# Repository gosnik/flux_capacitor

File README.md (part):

# flux_capacitor

Routing defaults to curved spline/PH realization, enabling compatible erosion and XPBD repair.
Straight routing remains an explicit option (`--straight-tracks`, or
`run_tiers.sh --track-geometry straight`).
Tier promotion still requires complete connectivity and original-project KiCad DRC.

Regional geometry repair enables bounded CPU AVBD refinement after eligible XPBD proposals,
including converged proposals and single-route obstacle scenes. It jointly updates trace controls and eligible generated vias using local blocks,
contact multipliers, adaptive penalties, and deterministic owner coloring under the shared CPU
worker budget. Via motion requires every attachment to be owned by the window; protected or
external attachments pin the via. PH reconstruction and exact copper checks still decide whether
a proposal survives. Use `--no-avbd-relaxation` for comparison or `--avbd-iterations N` (1–128)
to bound its iterations. `regional_avbd_*` metrics distinguish solver proposals from retained
regional improvements; neither implies a final DRC pass.

Regional search evaluates at most two selected windows before broad portfolio enumeration,
with prefix limits of eight alternatives, 1,024 bundle/lane states and 128 access states. Completed
navigation requests and prepared geometry are reused across continuations with exact input keys;
completed-route storage is capped at 512 entries and 64 MiB. The state engine schedules bounded
repair experiments under a shared deadline. Each eligible strategy receives initial exploration;
subsequent priority combines measured physical gain per active time with aging. Stagnation
suppresses only the same strategy and input state. Physical progress affects priority rather
than granting permission to continue. Legacy credit settings no longer gate execution.
Up to two paused experiments retain separate preparation caches. A full pool resumes live work
before admitting another strategy, exchanging slots without evicting the selected continuation.
Changed physical inputs invalidate a
paused regional solve before it can resume. History-only updates preserve its immutable search
snapshot; publication retains newer routing knowledge. Global retries still depend on history. Scheduling history is capped at roughly 4,096 dispatch records;
exact context keys have a 4,096-entry/64 MiB ceiling. Reaching these safety bounds retains the best
checkpoint and reports exhaustion. Linux also checks a cooperative 2 GiB process RSS threshold
when retaining paused experiments; this is not a hard allocator limit.
The engine retains its best physical scene; full-scene connectivity and DRC remain authoritative.

Terrain evolution and hydraulic GPU routing share immutable device-local walkability masks
through the common Vulkan runtime. Cache identity includes dimensions and exact normalized
contents; leases keep buffers alive through fenced submissions. The cache bounds both entries
and allocated device bytes (16 entries / 64 MiB) and evicts only idle entries. Exact host
identity mirrors consume up to another 64 MiB, plus bounded staging during upload. Mutable polygon rasterization uses a
private mask. Height feedback still uploads on every request.
`static_seed_height_evolution_gpu_mask_uploads`, `*_upload_reuses`, and
`*_cross_pipeline_reuses` distinguish transfers, cache hits, and reuse across the two pipelines;
the corresponding `static_seed_hydraulic_gpu_mask_*` counters cover hydraulic discovery.
XPBD retains its existing immutable-input cache. Mutable fields and incompatible geometry
layouts are not aliased across pipelines.

v0.140/schema 21 separates global physical feedback from continuous realization: intermediate
epochs perform bounded discrete corridor, packing, terminal, lane, layer, and via analysis, while
PH/XPBD/PNS, residual repair, quantization, and exact detailed routing run only on the retained
final checkpoint. PH optimization shares an immutable prepared NavMesh corridor, can certify
conservative sub-cell free-space slivers against the exact offset domain, scores seeds against
that same domain, and rejects GPU/CPU candidates that leave the selected homotopy. Exact
connectivity, represented copper DRC, and external KiCad DRC remain authoritative.

Residual regional failures now enter a bounded conflict-directed exact-master loop before the
broader cone/global retry. The existing finite template/access/via/lane CSP is the discrete master;
failed PH/copper realizations contribute stable physical no-good clauses, and only complete route
runs implicated by the failure receive new corridor, homotopy, layer, and via columns. PH geometry
stays outside the master and remains its separation oracle. A replacement is retained only as an
atomic feasibility-first improvement, with exact detailed connectivity and DRC still authoritative.
See [`ADR 0168`](docs/adr/0168-conflict-directed-exact-regional-master.md).

v0.138/schema 21 applies the source-bound KiCad hole-clearance floor as an exact
different-net drill-boundary-to-copper rule for straight tracks, arcs, vias, supported pads, and
saved zone fills. Whole-board and dynamic DRC share that predicate with global and regional route
screening. Mechanically drilled round holes alone participate in hole-to-hole checks; milled oval
holes remain exact copper-clearance obstacles, and laser-drilled microvias stop strict import until
their distinct fabrication semantics are represented. See
[`ADR 0167`](docs/adr/0167-source-bound-fabrication-rules-and-stackup.md).

v0.137/schema 21 preserves the saved physical board thickness and ordered KiCad stackup as
canonical source state. Copper, dielectric, mask, paste, and silkscreen entries retain their
physical order; dielectric `addsublayer` records retain independent material and thickness data;
and dielectric constant/loss tangent use deterministic decimal nanounits rather than binary
floating point. Source-preserving export and telemetry/replay carry the same state. Unrepresented
frequency-dependent dielectric fields stop strict import with an attributed diagnostic instead of
being silently discarded. See
[`ADR 0167`](docs/adr/0167-source-bound-fabrication-rules-and-stackup.md).

v0.136/schema 20 also extends the strict KiCad net-class snapshot to bind the matching saved
project revision and its board-wide fabrication floors. Track, clearance, via diameter, drill, and
annular-ring minima participate in rule resolution; exact circular/oval physical holes participate
in mechanical hole-to-hole DRC and early global/regional via-site rejection. KiCad remains the
project-rule authority, and unrepresented custom or region-dependent rules are not approximated as
if they were exact.

v0.129/schema 19 preserves a KiCad zone that has no saved fill as an immutable
`requires_refill` marker instead of discarding it or inventing copper. Canonical validation keeps
saved-fill and requires-refill states mutually exclusive. Ordinary detailed routing fails closed;
only the explicit `--refillable-zones` workflow may publish provisional copper, and KiCad refill,
strict re-import, connectivity, and external DRC remain mandatory. All nine pinned
KiCadRoutingTools fixtures now pass strict import in their original KiCad 10 syntax. See
[`ADR 0158`](docs/adr/0158-source-bound-unfilled-zones.md).

The same schema retains circular or oval pad-drill width/height and pad-local drill offset. Exact
non-plated circle/capsule obstacles replace the former maximum-diameter circle, and plated-hole
transition reuse now occurs at the physical hole centre rather than the pad anchor. Telemetry and
the viewer carry and render the same rotated drill geometry. See
[`ADR 0159`](docs/adr/0159-exact-pad-drill-geometry.md).

The native C++/Dear ImGui application for live router inspection and JSONL record/replay is
documented in [docs/router-telemetry-viewer.md](docs/router-telemetry-viewer.md). It visualizes
routes, rip-up activity, Pathfinder metrics, congestion and clearance conflicts, resource
occupancy, routing priority, and via-site decisions from `flux.telemetry.v1`.

The v0.128 router-side observer exposes global routing milestones, staged-priority evidence,
regional residual groups, attributed physical conflicts, bounded via candidates, and selected via
assignments through a bounded, read-only Boost.Beast server at
`ws://127.0.0.1:8765/telemetry` by default for KiCad routing and integrated-optimization commands;
`--no-telemetry` is the explicit headless opt-out. A preallocated non-blocking MPSC ring
isolates workers from the observer, while stable-ID coalescing and recovery snapshots let the
viewer recover current state. A separately cached immutable source snapshot supplies the viewer
with board outline/cutouts, layers/nets, footprint courtyards and pads, existing tracks/native arcs,
vias, zones, and keepouts without retransmitting the board in every dynamic snapshot. A stable
path-plus-revision identity lets the same observer retain multiple KiCad source scenes.
Selected global polylines are overlaid as provisional routes even when regional/detailed routing is
incomplete. Complete local quintic PH tessellations, selected regional vias, and their exact-static-
checked straight or dogleg run-ups are separate provisional overlays, so a via relocation is not
displayed as an unconnected marker. Detailed-copper, placement, and validation events remain
incremental follow-up coverage.
The activity table is newest-first, and compact regional `SearchSummary` events keep long PH
window realization observable after the global pass has finished. Chronological trace storage and
replay semantics are unchanged. Search-only bursts do not trigger unchanged recovery snapshots.

Connected coarse topology may proceed to exact detailed materialization when every regional window
has produced one complete atomic PH candidate, even if sampled PathFinder/shadow overflow
remains. Exact connectivity and copper DRC still reject the complete transaction. See
[`ADR 0153`](docs/adr/0153-exact-regional-handoff.md) and
[`ADR 0154`](docs/adr/0154-default-websocket-telemetry.md). Dense-board observability and the
current Freerouting control are recorded in
[`ADR 0155`](docs/adr/0155-dense-board-observability-and-external-control.md).

The optional continuous route representation is a tangent-continuous chain of quintic
Pythagorean-hodograph Bezier segments. PH Hermite interpolation, centripetal/chord parameter
selection, fairness-aware branch ranking, optional bounded geometric-G2 joining, polynomial speed
and arc length, analytical curvature and inflection isolation, and exact rational offsets replace
the former cubic B-spline implementation. XPBD and PNS move interpolation nodes and rebuild the PH
segments; telemetry publishes flattened six-control degree-five spans. Detailed routing uses a
resident Vulkan XPBD whole-chain precondition and candidate-major GPU polishing: every bounded
node-move wave is sampled/ranked on the device, while only a stable four-candidate shortlist pays
the recursive CPU shape/corridor certificate. Fine-grained certificates remain serial because
their recursive long tails measured worse when synchronized per node. Complete same-layer route
chains instead run as bounded parallel tasks against one immutable board snapshot; compact copper
deltas are reduced in stable route order and exact-rechecked before commit. CPU exact geometry,
connectivity, DRC, and commit remain authoritative, and unavailable compute restores the complete
CPU wave. KiCad has no electrical Bézier-track primitive, so each final regional PH candidate is
immediately fitted to native connected track arcs/segments and checked as that exact copper scene.
Native fitting checks quantized join angles and uses tangent-matched biarcs when independent
circle fitting would leave kinks. An ownership-resolved manifest carries those exact pieces into
detailed routing; assembled-scene feedback includes outside-window routes and proposed vias.
Arc navigation obstacles cover the actual sweep rather than filling the supporting circle.
Rational PH offsets remain targeted diagnostics for a rejected native scene rather than the normal
acceptance bottleneck. See [`ADR 0156`](docs/adr/0156-quintic-ph-continuous-routing.md) and
[`ADR 0171`](docs/adr/0171-fair-g2-native-copper-realization.md).
Residual retry now solves only transitive fragment-owner cones, reuses unaffected assignments,
and deterministically remaps derived channel/terminal/via identities before atomic checkpoint
replacement. Telemetry and CLI JSON distinguish reused, recomputed, and withheld assignments.
Prepared output validation and NavMesh routing now share cached polygon bounds, boundary indices,
inline immutable cell collections, and a cutout AABB hierarchy. Regional alternatives use
fail-closed local domains, bounded worker caches, clearance-capped distance queries, and indexed
lane-order screening. The completed isolated-ESC qualification takes 18:08.16 at 264,772 KiB peak
RSS and reports 288 reused plus 15 recomputed cone assignments with none withheld. It is still an
incomplete diagnostic checkpoint: 22 nets are unrouted, sampled overflow is 1,114, and 4,756
clearance-shadow conflicts remain, so no detailed copper or KiCad candidate is produced.

`flux_capacitor` is an experimental C++ engine for integrated PCB component placement
and track routing. Placement and routing share one board model so that routing pressure
can improve placement and bounded placement changes can resolve routing failures.

The current executable baseline provides:

- a versioned C++ board IR with integer-nanometre coordinates, stable typed IDs, and
  board-fixed or footprint-owned layer-aware keepouts, plus per-footprint allowed absolute
  rotations and front/back placement permissions;
- board/footprint/pad/track/via/filled-zone/layer/net models plus canonical
  multiple-net-class membership and inferred differential-pair identity with deterministic,
  per-property priority resolution; saved zone regions retain simple outer contours and exact
  hole contours;
- deterministic transforms and polygon/segment predicates over exact outer-board-minus-cutout
  material;
- structural and placement validation with machine-readable issue codes;
- multilayer connectivity analysis spanning pads, tracks, vias, and immutable physical
  filled-zone polygons;
- explicit pad geometry and board fallback plus per-net-class clearance, track, via,
  drill, and board-edge rules;
- shape-aware internal copper DRC for rotated circle, rectangle, oval, and
  round-rectangle pads, filled copper zones, and independent track/via/pad/pour keepout
  rules, with conservative fallbacks for explicitly lossy shapes;
- deterministic multilayer A* global routing with negotiated edge/node congestion,
  exact board-edge, indexed shape-aware foreign-copper, filled-zone, and track/via keepout
  obstacles,
  orthogonal off-grid pin access, vias, incremental multi-pin trees, capacity overflow,
  stagnation limits, deterministic per-resource demand/contributing-net evidence, and
  affected-cone checkpoint reuse with automatic geometric invalidation; planned width,
  via diameter, and foreign-net spacing use each net's resolved routing rules; conservative
  slicer-inspired scanline decomposition groups distinct free lanes into capacity-bearing
  corridor resources whose present/history congestion participates in PathFinder allocation;
  between unsuccessful passes, deterministic pressure-aware reroute ordering promotes unrouted
  and repeatedly congested nets inside their existing priority tier while keeping declared
  differential pairs and routing buses contiguous and ordered; an opt-in hybrid graph also lets
  PathFinder traverse independently rechecked capacity-bearing Voronoi chords directly instead of
  visiting every intermediate grid sample; explicitly bounded terminal neck-down access may
  recover an ordinary-net pin escape only after nominal width fails, every narrow segment passes
  exact represented clearance, and its grid portal remains legal at nominal width; an independent
  direct-medial policy can allocate a short exact chord at configured narrower demand only when
  nominal demand cannot fit and nominal-width disks remain legal at both transition portals; an
  opt-in stateful sampled-corridor policy constructs a second conservative narrow-width corridor
  graph and lets bounded A* width-mode runs cross multi-edge bottlenecks while charging their own
  physical corridor capacity; when shared medial capacity is enabled, every selected ordinary-net
  width contributes the same `width + 2 * clearance` envelope to PathFinder cost, overflow,
  packing, and checkpoint reuse; an opt-in late constructive phase can reject every transition
  that would exceed sampled, corridor, or selected-width shared physical capacity while retaining
  the best earlier negotiated checkpoint if no strict ordering completes; strict failures also
  retain directed occupying-net evidence, and an independently bounded singleton repair can rip
  complete same-pass blockers, retry first, and defer every victim for a fresh route;
- opt-in transactional KiCad zone-refill routing that treats saved pours as planning-time
  refillable geometry, emits only a provisional result from C++, refills a separate candidate
  through KiCad, and publishes it only after strict re-import and whole-board KiCad DRC;
- deterministic detailed materialization that simplifies global paths into tracks and
  spanning vias, transactionally reuses validated unaffected-net copper with stable IDs,
  falls back to full rematerialization when reuse is invalid, and rejects structurally
  invalid, disconnected, or DRC-illegal results, and materializes per-net resolved
  track/via dimensions unless an explicit run-wide override is requested; deterministic
  45-degree corner pull-tight shortens physical copper and falls back to the legal orthogonal
  route whenever exact checks reject a shortcut; bounded continuous centerline projection then
  shortens conventional polylines inside per-vertex trust regions, using deterministic halving
  to approach obstacle clearance, a run-wide exact-candidate budget, quantized local DRC probes,
  whole-board connectivity/DRC acceptance, and discrete fallback; opt-in strict-medial
  materialization can replace topology-complete resources with checked packed lane chords,
  accepted same-layer
  route-selected junction bridges whose shifted resource lines can meet at checked polyline
  miters, exact terminal joins, and multi-layer runs; complete differential pairs and
  ordered buses can select spacing-checked, order-preserving via arrays as one group transaction;
  mixed-width terminal and direct-medial paths can undergo bounded continuous refinement inside
  equal-width planar runs while every width/layer transition remains fixed, with exact local checks
  and transactional discrete fallback; detailed CLI results retain the governing global status,
  failing-net connectivity details, a copper-violation histogram, and one representative violation
  without exporting an illegal candidate;
  bounded group fanout synthesis preserves legal direct joins or packs ordered staircases at pad
  and layer-run boundaries, can translate a via array longitudinally to create escape run-up, and
  atomically falls back when exact clearance, gap, skew, connectivity, or board DRC rejects every
  candidate; edge-aligned terminal width metadata is simplified only inside equal-width runs and
  materialized as distinct straight KiCad segments; equal-width orthogonal corners can also
  receive deterministic 45-degree pull-tight without moving a width boundary; optional native
  curved fitting likewise operates only within equal-width same-layer runs and inherits that local
  width, while topology-locked replacement remains withheld for that path;
  opt-in post-allocation cubic B-spline routing preserves endpoint tangents, adaptively tessellates
  and fits native lines/arcs, builds exact collision envelopes, invokes bounded recursive PNS
  push-shove for unlocked straight blockers, updates the control corridor, and refits using local
  basis-weighted control displacements; all budgets and whole-transaction polyline fallback remain
  explicit; an independent opt-in
  post-route skew tuner adds ordinary rectangular polyline length to the shorter member of a
  freshly routed point-to-point constrained differential pair, packs one or more deterministic
  periods within explicit amplitude/spacing/candidate bounds, certifies every replacement chord
  against extracted polygonal free space, protects source and reused copper, and commits only after
  exact whole-board acceptance; an independent opt-in batch allocator retains several individually
  legal regions per pair and uses bounded exact conflict search to maximize simultaneously repaired
  pairs instead of committing by greedy pair order;
- deterministic orientation-aware analytical placement using weighted net centroids,
  mixed-size density repulsion, source anchoring, and exact courtyard/board/keepout
  legalization while preserving locked footprints; explicit rigid groups and intersecting
  relative-constraint graphs are projected onto common translations and legalized atomically,
  with one lock immobilizing the complete policy component; an opt-in routing-informed pass feeds
  bounded PathFinder congestion, width-reduction, and blocker escape targets into analytical
  attraction before exact legalization; an independent bounded simultaneous legalizer can assign
  several singleton or policy-component atoms to analytical/routing-guided sites together, making
  occupied-site exchanges legal without exposing an overlapping intermediate placement;
- a bounded deterministic integrated optimizer that tries legal unlocked-footprint moves,
  opt-in discrete rotations and side changes constrained by each footprint's hard orientation
  policy, opt-in atomic position swaps between route-ranked unlocked footprint pairs, and bounded
  rigid translations of explicit designer-declared placement groups; an additional opt-in
  neighborhood translates the complete fixed-point closure of intersecting relative constraints
  and rigid groups as one atomic route-guided component; it can
  evaluate a legalized global placement seed, globally reroutes every proposal,
  runs detailed connectivity and DRC, and accepts only lexicographic feasibility improvements;
  it derives bounded move targets from congestion hot spots, blocking-object geometry, and
  other-pin centroids when the evaluation budget is tight; local candidates use incremental
  global/detailed screening but require a full-board reroute and fresh copper materialization
  before acceptance;
  an explicit routed-quality mode continues beyond first feasibility, reduces actual global
  route cost, and stops only at a bounded local optimum or a truthful pass/evaluation limit;
  equally feasible candidates prefer lower normalized width-loss cost, then actual materialized
  route length, before abstract global search cost;
  every fresh fully routed, connected, and DRC-clean candidate also participates in a bounded
  deterministic Pareto archive across width loss, physical length, route cost, side/rotation
  changes, and placement displacement, without changing the active lexicographic search path;
- optional source-bound placement-move priority sidecars classify every footprint and stage
  cumulative move authorization from resistors and capacitors through transistors, other parts,
  miscellaneous ICs, MCUs, and SoCs, with connectors and pin headers unlocked only as a last
  resort; atomic transactions wait for their highest member tier, while locks and every exact
  placement/routing acceptance gate remain stronger than priority;
- bounded KiCad S-expression parsing and strict `.kicad_pcb` import for layers (including
  `power`-typed inner copper), nets, one outer outline with disjoint board/footprint-owned
  `Edge.Cuts` cutouts, footprints, courtyard provenance, pads, segments,
  track arcs, vias, simple or exactly unfractured saved copper-fill regions, and polygonal
  board/footprint rule areas with all five KiCad keepout categories preserved;
- source-preserving KiCad candidate export with content-derived stale-snapshot checks,
  immutable filled-zone preservation, deterministic UUID mapping, strict semantic round-trip
  verification, and refusal to overwrite an existing artifact;
- deterministic source-bound Specctra DSN export and routing-only SES import for black-box
  freerouting comparison, with exact source/DSN byte provenance, complete placement and protected
  copper verification, 100 nm session-grid checking, normalized deterministic route IDs, full
  connectivity/represented-DRC acceptance, and fail-closed unsupported geometry;
- deterministic source-bound orientation-constraint sidecars with strict stable-ID/reference
  validation, current-only template generation, scoped repair/refinement commands, and safe
  handoff of supported physical changes back to KiCad;
- deterministic source-bound placement-group sidecars with strict stable-ID/reference membership,
  empty non-inferential templates, disjoint group validation, and optimizer-only KiCad policy
  preservation;
- deterministic source-bound placement-region sidecars with explicit world polygons, stable
  footprint membership, full transformed-envelope containment, empty non-inferential templates,
  and hard enforcement across global and integrated placement;
- deterministic source-bound relative-placement sidecars that capture nominal anchor vectors from
  the immutable source and enforce inclusive reviewed X/Y deviation windows across all placement
  paths without inferring relationships from connectivity or proximity; version 2 additionally
  captures nominal radial distance and relative rotation and can enforce optional inclusive
  distance and circular microdegree windows;
- exact source representation of circular KiCad courtyards with conservative circumscribed search
  proxies, plus complete source-bound placement-envelope sidecars whose pad-derived suggestions
  remain unusable until every missing footprint is explicitly reviewed and approved; an
  independent opt-in may instead derive tentative pad/Fab/Silk bounds for proposal generation,
  while marking every resulting placement for mandatory post-process human review;
- a read-only `kicad-python` IPC bridge for explicit project net classes and effective per-net
  constituents, including differential-pair width/gap defaults, with deterministic source-bound
  snapshots consumed by every KiCad routing and optimization command;
- deterministic C++ source/candidate change sets that require byte-for-byte reproduction through
  the source-preserving exporter, inventory every live footprint and routing UUID, and describe
  exact footprint-transform previews plus track, arc, and via create/update/remove operations;
- a fail-closed `kicad-python` candidate bridge whose default mode only previews an exact live-board
  match and whose opt-in routing apply performs a second in-commit stale check, validates every
  returned object, and pushes one unsaved undo step; its offline validation mode exercises the
  current C++ change-set contract without requiring a running editor; live footprint apply remains
  withheld while current upstream whole-footprint updates can damage schematic linkage;
- a minimal routing-only KiCad workflow that packages measured free-space/PathFinder policies as
  the bounded `autoroute_v1` preset, requires a new candidate path, previews a source-bound change
  set, runs external KiCad CLI DRC when available, and permits live routing application only after
  that independent DRC passes;
- a bounded integrated `place_route_v1` KiCad workflow that runs analytical/routing-guided global
  placement and detailed routing together, defaults to the reviewable resistor-first/connector-last
  move policy, verifies a source-bound candidate and external KiCad DRC, reports exact human-review
  reasons, and withholds every placement result from live IPC application;
- deterministic source-bound differential-pair sidecars for explicit minimum physical gap and
  maximum routed skew constraints, applied as hard detailed-routing and optimization acceptance
  gates without pretending preferred KiCad net-class geometry is itself a DRC limit;
- a feasibility-first structured objective vector;
- confined conflict-directed anisotropic hydraulic erosion that produces bounded same-layer
  topology alternatives after an exact regional copper failure, with deterministic CPU/Vulkan
  parity and unchanged polygon, clearance, connectivity, and DRC authority;
- a deterministic CLI demonstration and dependency-free CTest suite.

Safe live footprint transforms, transactional zone refill/editing and ambiguous fill contours,
non-courtyard circular graphics, custom rules, gridless/shove detailed routing, scalable density
models, spatially incremental DRC, and richer PCB electrical constraints are the next milestones.
See
[AGENTS.md](AGENTS.md) for the engineering contract and research-backed roadmap.

Architectural decisions are recorded in [`docs/adr`](docs/adr), beginning with the
canonical board core and negotiated-congestion routing baseline.

## Build and test

Requirements: CMake 3.25+, Ninja, a C++20 compiler, Boost 1.75+ with Boost.JSON, OpenSSL 3,
Vulkan headers/loader, `glslc`, and a Vulkan 1.1 compute-capable GPU with a working driver. GPU
acceleration is a
mandatory Flux runtime requirement: configuration fails without the Vulkan toolchain and routing
fails closed if a compute device cannot execute the startup probe. The deterministic CPU hydraulic
implementation is retained only as a test/oracle backend, not as a production fallback.
Boost.Polygon supplies the permissively licensed integer segment-site Voronoi builder; all
resulting graph chords are quantized and rechecked by Flux before use.

```sh
cmake --preset dev
cmake --build --preset dev
ctest --preset dev
```

An AddressSanitizer/UndefinedBehaviorSanitizer preset is also available on supported
GCC/Clang systems:

```sh
cmake --preset asan
cmake --build --preset asan
ctest --preset asan
```

## CLI baseline

The shortest usable path creates a new routed candidate, verifies its exact source-bound change
set, and runs KiCad CLI DRC when `kicad-cli` is installed:

```sh
python3 plugins/kicad/route_board.py \
  --board board.kicad_pcb \
  --output board.flux-routed.kicad_pcb \
  --flux-cli ./build/dev/flux-cli
```

Add `--capture-netclasses` while the matching saved board is open in KiCad to capture authoritative
project rules through the read-only IPC bridge. Alternatively pass an existing source-bound
snapshot with `--netclasses`. Preview is offline and non-mutating. After reviewing it,
`--apply-routing` applies tracks/arcs/vias to the matching open board as one unsaved undo step and
requires an external KiCad DRC pass. The workflow never saves KiCad and refuses existing output
files.

For an explicit provisional zone-refill transaction with the crossing-safe diagonal graph and
native cubic B-spline/PNS line-arc fitting, use:

```sh
python3 plugins/kicad/route_board.py \
  --board board.kicad_pcb \
  --output board.flux-curved.kicad_pcb \
  --flux-cli ./build/dev/flux-cli \
  --refillable-zones \
  --curved-traces
```

This path always refills zones in a separate file, strictly re-imports it, runs KiCad CLI DRC, and
requires human review. It cannot apply routing directly to the open editor.

For a congested refillable board, add `--repair-sampled-conflicts`. After the negotiated pass it
preserves every unaffected route and visits at most two layer-local conflict tiles in stable
pressure order, with at most 12 hard-capacity passes per cone. Every sampled, shared-physical, and
clearance-shadow participant in the selected cone is invalidated; terminal portals are diversified
and the complete participating nets are rerouted with hard capacity. A non-improving repair is
discarded transactionally.

To inspect an unsuccessful run in KiCad, add `--keep-incomplete-preview` and choose a new output
name. The wrapper retains the materialized layout, reports `ok: false` plus a `review_only`
`incomplete_preview`, and returns Flux's nonzero status. Zone refill, external approval, and live
application are deliberately withheld. The lower-level equivalent is `detail-kicad BOARD
--write-incomplete-preview OUTPUT`.

For integrated placement plus routing, use the same bridge in candidate-only mode:

```sh
python3 plugins/kicad/route_board.py \
  --board board.kicad_pcb \
  --output board.flux-place-routed.kicad_pcb \
  --flux-cli ./build/dev/flux-cli \
  --integrated-placement
```

`place_route_v1` defaults to two placement passes, 64 routed candidate evaluations, routing-guided
global placement, and suggested staged move priorities. Pass a reviewed source-bound policy with
`--placement-move-priorities` to replace the prefix-derived classification. Use
`--tentative-envelopes` only when provisional pad/Fab/Silk bounds and mandatory mechanical review
are acceptable. The output remains a new file-level candidate even after external KiCad DRC;
`--apply-routing` is deliberately rejected in this mode because the live bridge does not mutate
footprints. See [`ADR 0112`](docs/adr/0112-bounded-kicad-place-route-workflow.md).

```sh
./build/dev/flux-cli version
./build/dev/flux-cli demo
./build/dev/flux-cli demo-invalid
./build/dev/flux-cli route-demo
./build/dev/flux-cli route-demo --strict-medial
./build/dev/flux-cli route-demo --strict-medial --direct-medial
./build/dev/flux-cli free-space-demo
./build/dev/flux-cli incremental-route-demo
./build/dev/flux-cli detail-demo
./build/dev/flux-cli detail-demo --strict-medial
./build/dev/flux-cli incremental-detail-demo
./build/dev/flux-cli optimize-demo
./build/dev/flux-cli orientation-optimize-demo
./build/dev/flux-cli group-optimize-demo
./build/dev/flux-cli constraint-global-optimize-demo
./build/dev/flux-cli routing-guided-global-optimize-demo
./build/dev/flux-cli refine-demo
./build/dev/flux-cli global-optimize-demo
./build/dev/flux-cli inspect-kicad board.kicad_pcb
./build/dev/flux-cli inspect-free-space-kicad board.kicad_pcb NET_NAME F.Cu --shared-domain
./build/dev/flux-cli constraints-template-kicad board.kicad_pcb
./build/dev/flux-cli envelopes-template-kicad board.kicad_pcb
./build/dev/flux-cli diffpairs-template-kicad board.kicad_pcb
./build/dev/flux-cli buses-template-kicad board.kicad_pcb
./build/dev/flux-cli placement-move-priorities-template-kicad board.kicad_pcb > board.flux_move_priorities
./build/dev/flux-cli autoroute-kicad board.kicad_pcb board.flux-routed.kicad_pcb
./build/dev/flux-cli route-kicad board.kicad_pcb
./build/dev/flux-cli route-kicad board.kicad_pcb --multisource-steiner
./build/dev/flux-cli route-kicad board.kicad_pcb --atomic-net-trees
./build/dev/flux-cli route-kicad board.kicad_pcb --atomic-net-trees --selective-congestion-reroute
./build/dev/flux-cli route-kicad board.kicad_pcb --atomic-net-trees --selective-congestion-reroute --selective-full-reroute-interval 3
./build/dev/flux-cli route-kicad board.kicad_pcb --max-expansions 10000 --expansion-retry-heuristic-weight-per-mille 10000
./build/dev/flux-cli route-kicad board.kicad_pcb --max-expansions 10000 --expansion-retry-heuristic-weight-per-mille 10000 --reuse-weighted-search-frontier
./build/dev/flux-cli route-kicad board.kicad_pcb --present-congestion-multiplier-per-mille 1300 --max-present-congestion-scale-per-mille 10000 --present-congestion-escalation-start-iteration 4
./build/dev/flux-cli route-kicad board.kicad_pcb --strict-medial --direct-medial
./build/dev/flux-cli route-kicad board.kicad_pcb --terminal-neck-down-width-nm 150000 --max-terminal-neck-down-length-nm 3000000
./build/dev/flux-cli route-kicad board.kicad_pcb --direct-medial --medial-neck-down-width-nm 150000 --max-medial-neck-down-length-nm 3000000
./build/dev/flux-cli route-kicad board.kicad_pcb --corridor-neck-down-width-nm 150000 --max-corridor-neck-down-length-nm 3000000 --max-corridor-neck-down-states 5000000
./build/dev/flux-cli route-kicad board.kicad_pcb --corridor-neck-down-width-nm 150000 --max-corridor-neck-down-length-nm 3000000 --max-corridor-neck-down-states 5000000 --width-reduction-cost-per-grid-step 0
./build/dev/flux-cli route-kicad board.kicad_pcb --max-voronoi-resource-segment-length-nm 1000000
./build/dev/flux-cli detail-kicad board.kicad_pcb
# Default: straight track sections with conventional corner pull-tight.
./build/dev/flux-cli detail-kicad board.kicad_pcb board.straight.kicad_pcb
# Optional retained PH/spline realization:
./build/dev/flux-cli detail-kicad board.kicad_pcb --arcs board.curved.kicad_pcb
./build/dev/flux-cli detail-kicad board.kicad_pcb --netclasses board.flux_netclasses
./build/dev/flux-cli detail-kicad board.kicad_pcb --netclasses board.flux_netclasses --diffpairs board.flux_diffpairs --buses board.flux_buses
./build/dev/flux-cli detail-kicad board.kicad_pcb --diffpairs board.flux_diffpairs --tune-differential-pair-skew
./build/dev/flux-cli detail-kicad board.kicad_pcb --diffpairs board.flux_diffpairs --batch-assign-differential-pair-skew
./build/dev/flux-cli optimize-kicad board.kicad_pcb
./build/dev/flux-cli optimize-kicad board.kicad_pcb --placement-move-priorities board.flux_move_priorities
./build/dev/flux-cli optimize-kicad board.kicad_pcb --suggested-placement-move-priorities
./build/dev/flux-cli optimize-kicad board.kicad_pcb --envelopes board.flux_envelopes
./build/dev/flux-cli optimize-kicad board.kicad_pcb board.optimized.kicad_pcb
./build/dev/flux-cli global-optimize-kicad board.kicad_pcb
./build/dev/flux-cli global-optimize-kicad board.kicad_pcb --assignment-global-placement
./build/dev/flux-cli global-optimize-kicad board.kicad_pcb --tentative-envelopes
./build/dev/flux-cli global-optimize-kicad board.kicad_pcb board.optimized.kicad_pcb
./build/dev/flux-cli constrained-optimize-kicad board.kicad_pcb board.constraints
./build/dev/flux-cli constrained-refine-kicad board.kicad_pcb board.constraints board.refined.kicad_pcb
```

Regional candidate learning-to-rank is an opt-in experiment. Collect exact post-realization labels
without changing candidate order, train the external XGBoost model, then enable advisory ranking:

```bash
./build/dev/flux-cli detail-kicad board.kicad_pcb \
  --regional-candidate-training-data build/regional-candidates.jsonl
python3 tools/train_regional_candidate_ranker.py \
  build/regional-candidates.jsonl --output build/regional-ranker.json
./build/dev/flux-cli detail-kicad board.kicad_pcb \
  --regional-candidate-ranker-model build/regional-ranker.json \
  --regional-candidate-training-data build/regional-ranked-candidates.jsonl
```

Training requires the Python `xgboost` and `numpy` packages; routing does not. The exported model
uses a bounded Flux-owned JSON schema and can only reorder the already retained regional
shortlist. Invalid models restore the deterministic heuristic order, and every candidate that is
tried still passes the unchanged PH/XPBD, quantization, connectivity, copper-DRC, and transaction
gates. CLI JSON reports model loading, scored/reordered candidates, observation writes, and any
fallback diagnostic.

`demo` evaluates a small legal routed board and prints a machine-readable objective.
`demo-invalid` deliberately overlaps two courtyards and exits with status 2.
`route-demo` runs the planning-stage global router on the unrouted demo board.
`free-space-demo` runs the net/layer polygonal extraction, conservative integer offset, and
exact-rechecked Voronoi graph pipeline and reports regions, graph topology, withheld curves, and
peak width-dependent lane capacity. Its diagnostics distinguish unsupported obstacles from
identified conservative envelopes used for curved pads, tracks, and vias.
`incremental-route-demo` moves one terminal, reroutes its affected net, and reuses the
compatible path for a second net from the prior global-route checkpoint.
`detail-demo` materializes the global plan as checked physical copper. `--strict-medial` also
requires audited medial transitions and attempts topology-locked packed-lane copper;
`--direct-medial` opts capacity-certified Voronoi chords into PathFinder adjacency and may be
combined with strict mode. JSON distinguishes accepted lane paths, per-path evidence fallback,
and whole-candidate transactional fallback.
`incremental-detail-demo` preserves the stable track object for an unaffected net while
transactionally replacing the changed net and checking the combined board.
`optimize-demo` demonstrates blocking-object geometry and net context producing a useful
placement proposal under a one-move evaluation budget, followed by rerouting and legality
checks.
`orientation-optimize-demo` explicitly enables a 180-degree alternative on a footprint whose
hard allowed set is `{0, 180}`, and shows an offset surface terminal rotating across an
otherwise impassable routing barrier. Rotation and side search are disabled by default, and
run-wide alternatives cannot bypass per-footprint constraints. Side changes remap front/back
pad and owned-keepout layers internally, but source-preserving KiCad export currently rejects
them because a safe flip must rewrite every layer-bearing footprint construct.
`constraint-global-optimize-demo` projects a three-footprint component formed by an intersecting
rigid group and relative constraint onto one analytical translation, legalizes it atomically, and
accepts the seed only after it repairs two blocked routes. JSON reports component counts and one
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
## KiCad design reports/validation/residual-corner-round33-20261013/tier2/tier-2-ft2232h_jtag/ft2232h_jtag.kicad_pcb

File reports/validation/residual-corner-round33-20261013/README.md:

# Round33 — measured pad-core quantization guard

## Round33 — Geometry-dependent pad quantization bound (2026-10-13)

### Failure
Round32 retains lawful curved Tier2 copper but one residual GND corner cannot pass the strict transaction DRC. All nine radii report324998nm arc-centreline distance versus325000nm required at an axis-aligned rectangular pad. Connectivity and fitted tangents are intact.

### Earliest cause and experiment
The pad-arc distance kernel unconditionally subtracts2nm for vertex quantization, including exactly represented integer pad cores. This is a conservative lower bound, not evidence of actual2nm intrusion. Replace the constant with an upward-rounded bound on the maximum actual vertex rounding displacement. Point/segment/convex polygon distance is Lipschitz under that Hausdorff displacement; subtracting the bound remains conservative and becomes zero when no quantization occurs. Rounded-core radius is unchanged. No clearance tolerance is added, no corner is exempted, and every local transaction still passes strict DRC and pad preservation. Verify exact axis-aligned contact/boundary and rotated fractional geometry before benchmark promotion.

### Results and decision
All11 regression targets and independent implementation review pass. Sequential telemetry Tier0/1 remain byte-identical with zero KiCad DRC and opens (30.879s/106.809s detailed). Frozen source hash verification reports no drift.

Tier2 now passes:131/131 scaffold requests, zero physical opens, zero internal copper violations, zero unrounded bends,421 Beziers/164 arcs/889 tracks/75 vias. All164 residual bend repairs succeed. Authoritative exported KiCad error-severity DRC reports zero violations and opens. Planning161.160s; the separate end-to-end detailed command224.166s, including its own planning. PeakRSS725652KiB. Final copper layers were visually inspected (B.Cu is byte-identical to the previously inspected Round32 image).

The original harness exit1 is solely its intentional promotion guard; independent review confirms a final, non-preview, exported candidate passed all qualification gates. Promote Tier2 to qualified with30 iterations and unlock Tier3. The original exit/result remain unchanged as evidence.

Fresh sequential Tier3 remains51/148 with97 physical opens,279 tracks/20 vias,140.707s, peakRSS559696KiB, iteration limit. No final curved materialization. KRT's matched Tier3 run leaves83 opens in162.172s. Keep this general geometry correction and the Tier2 promotion; Tier3 is the next frontier.

Manifest preflight passes after promotion. Independent Tier3 scaffold export confirms97 opens and only the28 inherited footprint/silkscreen warnings; no added clearance/hole violations.

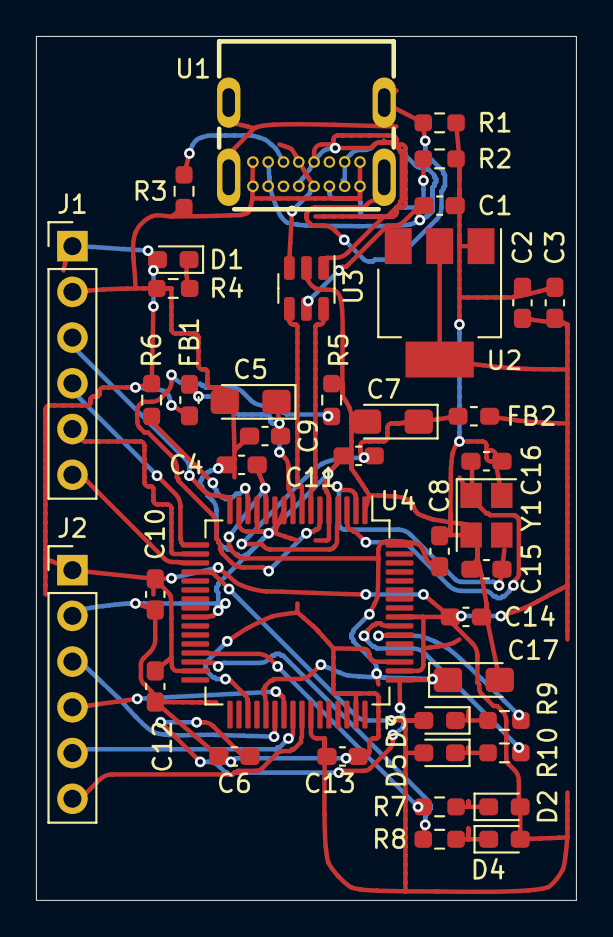
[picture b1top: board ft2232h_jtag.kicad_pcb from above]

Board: 2 copper layers, 30.0 x 48.0 mm, 41 parts (0 on the bottom side), 34 nets.

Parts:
C1, C3: 10uF; C_0603_1608Metric_Pad1.08x0.95mm_HandSolder
C2, C4, C6, C8, C9, C10, C11, C12, C13, C14: 100nF; C_0603_1608Metric_Pad1.08x0.95mm_HandSolder
C5, C7: 4.7uF; CP_EIA-3216-18_Kemet-A_Pad1.58x1.35mm_HandSolder
C15, C16: 30pF; C_0603_1608Metric_Pad1.08x0.95mm_HandSolder
C17: 3.3uF; CP_EIA-3216-18_Kemet-A_Pad1.58x1.35mm_HandSolder
D1, D4, D5: RED; LED_0603_1608Metric_Pad1.05x0.95mm_HandSolder
D2, D3: GREEN; LED_0603_1608Metric_Pad1.05x0.95mm_HandSolder
FB1, FB2: 40@100MHz; L_0603_1608Metric_Pad1.05x0.95mm_HandSolder
J1, J2: Pin Header 2.54 mm; PinHeader_1x06_P2.54mm_Vertical
R1: 0; R_0603_1608Metric_Pad0.98x0.95mm_HandSolder
R2, R3: 5.1k; R_0603_1608Metric_Pad0.98x0.95mm_HandSolder
R4, R6, R7, R8, R9, R10: 1k; R_0603_1608Metric_Pad0.98x0.95mm_HandSolder
R5: 12k; R_0603_1608Metric_Pad0.98x0.95mm_HandSolder
U1: TYPEC-306DDW-ARP16; USB-C-TH_TYPEC-306DDW-ARP16
U2: AMS1117-3.3; SOT-223-3_TabPin2
U3: USBLC6-2SC6; SOT-23-6
U4: FT2232HL; LQFP-64_10x10mm_P0.5mm
Y1: 12MHz; Crystal_SMD_3225-4Pin_3.2x2.5mm

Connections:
+1V8: C4.2, C6.2, C8.2, C17.1, U4.12 (VCORE), U4.37 (VCORE), U4.49 (VREGOUT), U4.64 (VCORE)
+3.3V: C2.1, C3.1, C10.2, C12.2, C13.2, C14.2, D1.2 (A), D2.2 (A), D3.2 (A), D4.2 (A), D5.2 (A), FB1.1, FB2.1, J1.1, J2.1, R6.1, U2.2 (VO), U4.20 (VCCIO), U4.31 (VCCIO), U4.42 (VCCIO), U4.50 (VREGIN), U4.56 (VCCIO)
/OSCI: C15.2, U4.2 (OSCI), Y1.3
/OSCO: C16.2, U4.3 (OSCO), Y1.1
/REF: R5.2, U4.6 (REF)
/RXLED_A: R7.1, U4.29 (ACBUS3)
/RXLED_B: R9.1, U4.54 (BCBUS3)
/TCK_TXD_A: J1.3, U4.16 (ADBUS0)
/TCK_TXD_B: J2.3, U4.38 (BDBUS0)
/TDI_RXD_A: J1.4, U4.17 (ADBUS1)
/TDI_RXD_B: J2.4, U4.39 (BDBUS1)
/TDO_A: J1.5, U4.18 (ADBUS2)
/TDO_B: J2.5, U4.40 (BDBUS2)
/TMS_A: J1.6, U4.19 (ADBUS3)
/TMS_B: J2.6, U4.41 (BDBUS3)
/TXLED_A: R8.2, U4.30 (ACBUS4)
/TXLED_B: R10.2, U4.55 (BCBUS4)
/USB_CONN_D+: U1.A6 (DP1), U1.B6 (DP2), U3.3 (I/O2)
/USB_CONN_D-: U1.A7 (DN1), U1.B7 (DN2), U3.1 (I/O1)
/USB_D+: U3.4 (I/O2), U4.8 (DP)
/USB_D-: U3.6 (I/O1), U4.7 (DM)
/VPHY: C7.1, C11.1, FB2.2, U4.4 (VPHY)
/VPLL: C5.1, C9.1, FB1.2, U4.9 (VPLL)
/~RESET: R6.2, U4.14 (~RESET)
GND: C1.2, C2.2, C3.2, C4.1, C5.2, C6.1, C7.2, C8.1, C9.2, C10.1, C11.2, C12.1, C13.1, C14.1, C15.1, C16.1, C17.2, J1.2, J2.2, R1.2, R2.2, R3.2, R4.1, R5.1, U1.A1 (GND), U1.A12 (GND), U1.B1 (GND), U1.B12 (GND), U2.1 (GND), U3.2 (GND), U4.1 (GND), U4.5 (GND), U4.10 (AGND), U4.11 (GND), U4.13 (TEST), U4.15 (GND), U4.25 (GND), U4.35 (GND), U4.47 (GND), U4.51 (GND), Y1.2, Y1.4
unnamed: D1.1 (K), R4.2
unnamed: D2.1 (K), R7.2
unnamed: D3.1 (K), R9.2
unnamed: D4.1 (K), R8.1
unnamed: D5.1 (K), R10.1
unnamed: R2.1, U1.A5 (CC1)
unnamed: R3.1, U1.B5 (CC2)
unnamed: R1.1, U1.17 (SHIELD), U1.18 (SHIELD), U1.19 (SHILED), U1.20 (SHIELD)
VBUS: C1.1, U1.A4 (VBUS), U1.A9 (VBUS), U1.B4 (VBUS), U1.B9 (VBUS), U2.3 (VI), U3.5 (VBUS)

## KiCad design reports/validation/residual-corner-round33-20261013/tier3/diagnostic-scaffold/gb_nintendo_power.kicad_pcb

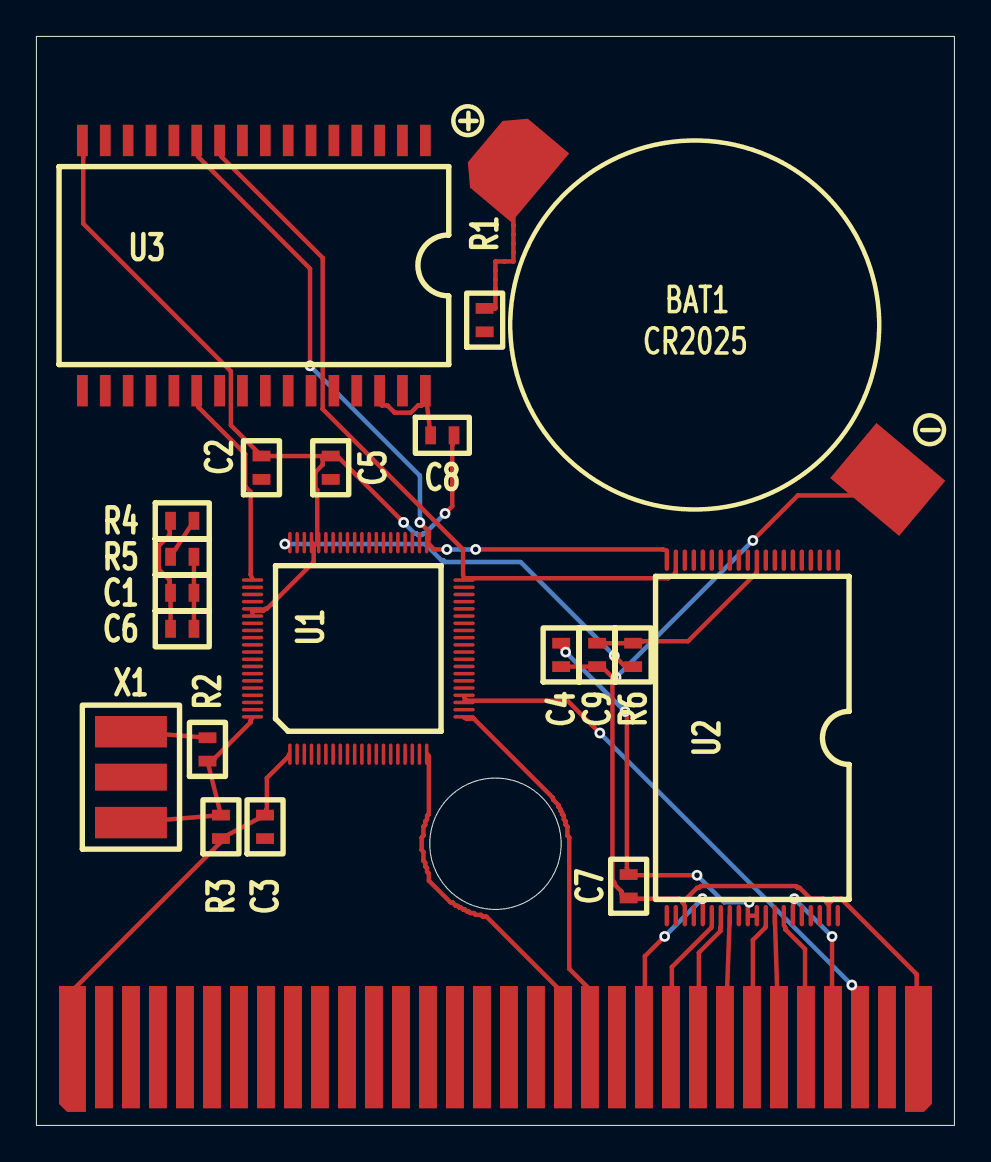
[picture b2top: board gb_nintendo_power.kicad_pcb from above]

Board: 2 copper layers, 51.0 x 60.5 mm, 22 parts (0 on the bottom side), 65 nets.

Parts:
BT1: CR2025; CR2025 Battery
C1: 150 nF; SMD Passive
C2: 120 nF; SMD Passive
C3, C4, C5, C6, C7, C8: 10 nF; SMD Passive
C9: DNP; SMD Passive
Hole: MountingHole_8.4mm_M8
J1: Cart_Edge_Connector; Edge Connector
R1: 1 kOhm; SMD Passive
R2, R4: DNP; SMD Passive
R3: 10kOhm; SMD Passive
R5: 10 kOhm; SMD Passive
R6: 0; SMD Passive
U1: G-MMC1
U2: FLASH
U3: SRAM
X1: Unpopulated; Crystal

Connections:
/A0.Out: U1.25 (A0.Out), U2.21 (A0), U3.12 (A0)
/A0.Sys: J1.6 (A0), U1.6 (A0.Sys)
/A1.Out: U1.41 (A1.Out), U2.20 (A1), U3.11 (A1)
/A1.Sys: J1.7 (A1), U1.7 (A1.Sys)
/A2.Out: U1.40 (A2.Out), U2.19 (A2), U3.10 (A2)
/A2.Sys: J1.8 (A2), U1.8 (A2.Sys)
/A3.Out: U1.39 (A3.Out), U2.18 (A3), U3.9 (A3)
/A3.Sys: J1.9 (A3), U1.9 (A3.Sys)
/A4.Out: U1.36 (A4.Out), U2.17 (A4), U3.8 (A4)
/A4.Sys: J1.10 (A4), U1.10 (A4.Sys)
/A5.Out: U1.35 (A5.Out), U2.16 (A5), U3.7 (A5)
/A5.Sys: J1.11 (A5), U1.11 (A5.Sys)
/A6.Out: U1.34 (A6.Out), U2.15 (A6), U3.6 (A6)
/A6.Sys: J1.12 (A6), U1.13 (A6.Sys)
/A7.Out: U1.32 (A7.Out), U2.14 (A7), U3.5 (A7)
/A7.Sys: J1.13 (A7), U1.14 (A7.Sys)
/A8.Out: U1.31 (A8.Out), U2.8 (A8), U3.27 (A8)
/A8.Sys: J1.14 (A8), U1.15 (A8.Sys)
/A9.Out: U1.30 (A9.Out), U2.7 (A9), U3.26 (A9)
/A9.Sys: J1.15 (A9), U1.16 (A9.Sys)
/A10.Out: U1.37 (A10.Out), U2.36 (A10), U3.23 (A10)
/A10.Sys: J1.16 (A10), U1.17 (A10.Sys)
/A11.Out: U1.29 (A11.Out), U2.6 (A11), U3.25 (A11)
/A11.Sys: J1.17 (A11), U1.18 (A11.Sys)
/A12.Out: U1.27 (A12.Out), U2.5 (A12), U3.4 (A12)
/A12.Sys: J1.18 (A12), U1.19 (A12.Sys)
/A13.Out: U1.26 (A13.Out), U2.4 (A13), U3.28 (A13)
/A13.Sys: J1.19 (A13), U1.20 (A13.Sys)
/A14.Out: U1.42 (A14.Out), U2.3 (A14), U3.3 (A14)
/A14.Sys: J1.20 (A14), U1.21 (A14.Sys)
/A15.Out: U1.43 (A15.Out), U2.2 (A15), U3.31 (A15)
/A15.Sys: J1.21 (A15), U1.22 (A15.Sys)
/A16.Out: U1.44 (A16.Out), U2.1 (A16), U3.2 (A16)
/A17.Out: U1.45 (A17.Out), U2.40 (A17)
/A18.Out: U1.46 (A18.Out), U2.13 (A18)
/A19.Out: U1.47 (A19.Out), U2.37 (A19)
/Batt.VCC: R1.1, U1.62 (Batt.VCC)
/D0: J1.22 (Data_0), U1.75 (D0), U2.25 (D0), U3.13 (D0)
/D1: J1.23 (Data_1), U1.76 (D1), U2.26 (D1), U3.14 (D1)
/D2: J1.24 (Data_2), U1.77 (D2), U2.27 (D2), U3.15 (D2)
/D3: J1.25 (Data_3), U1.74 (D3), U2.28 (D3), U3.17 (D3)
/D4: J1.26 (Data_4), U1.73 (D4), U2.32 (D4), U3.18 (D4)
/D5: J1.27 (Data_5), U1.72 (D5), U2.33 (D5), U3.19 (D5)
/D6: J1.28 (Data_6), U1.71 (D6), U2.34 (D6), U3.20 (D6)
/D7: J1.29 (Data_7), U1.70 (D7), U2.35 (D7), U3.21 (D7)
/GND: BT1.2 (-), C1.1, C2.2, C3.1, C4.1, C5.2, C6.1, C7.1, C8.2, C9.1, J1.32 (GND), R4.1, U1.2 (GND), U1.12 (GND), U1.28 (GND), U1.38 (GND), U1.48 (GND), U1.56 (GND), U1.57 (GND), U1.65 (GND), U1.66 (GND), U1.68 (GND), U1.78 (GND), U2.23 (GND), U2.39 (GND), U3.16 (GND), X1.2
/P10.R6: R6.1, U1.60 (Flash.P10.R6)
/SRAM.VCC: C8.1, U1.64 (SRAM.VOUT), U3.30 (CE2), U3.32 (VCC)
/SRAM.~CE1: U1.61 (SRAM.~CE1), U3.22 (~CE1)
/VCC: C1.2, C3.2, C4.2, C5.1, C6.2, C7.2, J1.1 (+5V), R3.1, R5.2, U1.1 (VCC), U1.33 (VCC), U1.53 (VCC), U1.63 (VCC), U1.69 (VCC), U2.30 (VCC), U2.31 (VCC)
/~CS.Sys: J1.5 (CS), U1.5 (~CS.Sys)
/~Flash.CE: U1.49 (Flash.~CE), U2.22 (~CE)
/~Flash.Reset: C9.2, R6.2, U1.55 (Flash.~RESET), U2.10 (~RESET)
/~Flash.WP: U1.50 (Flash.~WP), U2.12 (~WP)
/~OE.Out: U1.51 (~OE.Out), U2.24 (~OE), U3.24 (~OE)
/~Read.Sys: J1.4 (Read), U1.4 (~Read.Sys)
/~Reset.Sys: J1.30 (Reset), U1.23 (~Reset.Sys), U1.24 (~Reset.Sys)
/~WE.Out: U1.52 (~WE.Out), U2.9 (~WE), U3.29 (~WE)
/~Write.Sys: J1.3 (Write), U1.3 (~Write.Sys)
unnamed: BT1.1 (+), R1.2
unnamed: C2.1, U1.59
unnamed: R4.2, R5.1, U1.67
unnamed: R2.1, R3.2, U1.80 (Clk.In), X1.1
unnamed: R2.2, U1.79 (Clk.Out), X1.3
unnamed: U1.54, U1.58

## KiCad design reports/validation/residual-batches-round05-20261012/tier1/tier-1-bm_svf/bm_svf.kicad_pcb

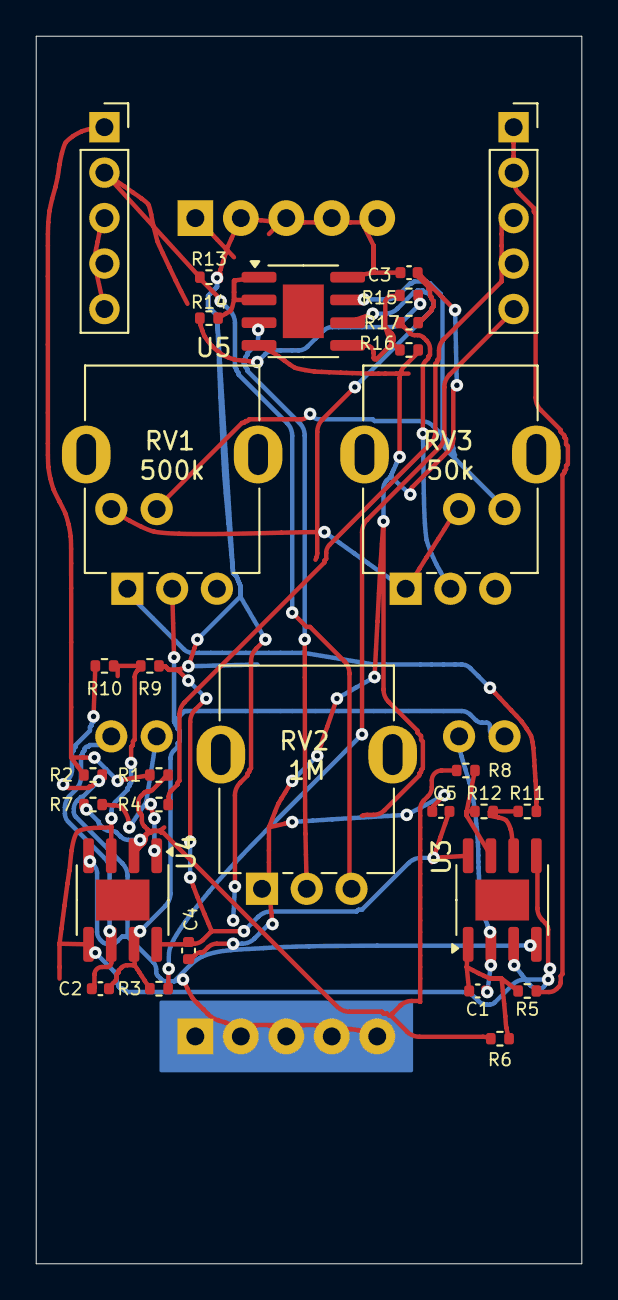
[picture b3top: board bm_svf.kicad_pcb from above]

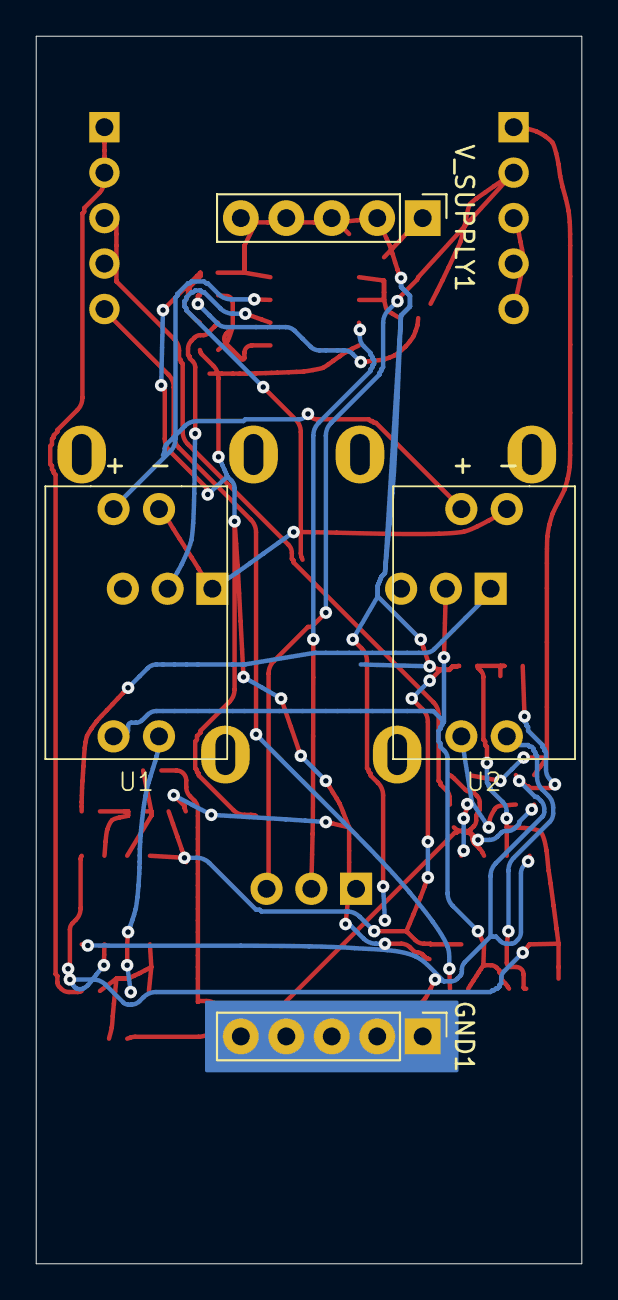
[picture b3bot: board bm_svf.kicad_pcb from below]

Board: 2 copper layers, 30.5 x 68.6 mm, 34 parts (4 on the bottom side), 25 nets.

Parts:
C1, C2: 10nf; C_0402_1005Metric
C3, C4, C5: 0.1uf; C_0402_1005Metric
GND1: Conn_01x05_Pin; Power_Connector
INPUT1: Conn_01x05_Socket; PinSocket_1x05_P2.54mm_Vertical
OUTPUT1: Conn_01x05_Socket; PinSocket_1x05_P2.54mm_Vertical
R1, R11, R12: 51k; R_0402_1005Metric
R2: 22k; R_0402_1005Metric
R3, R4, R5, R9, R10, R14: 1k; R_0402_1005Metric
R6, R7, R8: 10k; R_0402_1005Metric
R13: 100k; R_0402_1005Metric
R15, R16: 1M; R_0402_1005Metric
R17: 5.1k; R_0402_1005Metric
RV1: 500k; Potentiometer_RV09
RV2: 1M; Potentiometer_RV09
RV3: 50k; Potentiometer_RV09
U1, U2: VTL5C
U3, U4, U5: MCP6002-xSN; SOIC-8-1EP_3.9x4.9mm_P1.27mm_EP2.29x3mm
V_SUPPLY1: Conn_01x05_Pin; Power_Connector

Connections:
GND: C3.2, C4.2, C5.2, GND1.1, GND1.2, GND1.3, GND1.4, GND1.5, R2.1, R10.2, R16.1, R17.1, RV2.1, U3.4 (V-), U4.4 (V-), U5.4 (V-)
unnamed: C1.2, R5.1, R6.1, U3.1
unnamed: C2.2, R3.1, RV1.2, U1.4, U4.7
unnamed: INPUT1.3, INPUT1.4, INPUT1.5
unnamed: R4.1, R7.2, U2.4, U4.1
unnamed: R11.2, RV1.1
unnamed: R8.1, R12.1, U3.7
unnamed: R14.1, R15.2
unnamed: R17.2, RV3.2
unnamed: C1.1, U1.3, U3.2 (-)
unnamed: R11.1, R12.2, U3.6 (-)
unnamed: R1.2, R6.2, R7.1, R8.2, U4.2 (-)
unnamed: C2.1, U2.3, U4.6 (-)
unnamed: RV2.2, U5.3 (+)
unnamed: R14.2, U5.1, U5.2 (-)
unnamed: R15.1, R16.2, U5.5 (+)
VACTROL_NEG: RV3.1, U1.1 (-), U2.1 (-), U5.6 (-)
VACTROL_POS: U1.2 (+), U2.2 (+), U5.7
V_BF: OUTPUT1.5, R3.2
V_CV: INPUT1.2, R13.1, RV2.3
V_HF: OUTPUT1.3, OUTPUT1.4, R4.2
V_IN: INPUT1.1, R1.1, R2.2
V_LF: OUTPUT1.1, OUTPUT1.2, R5.2
V_MID: R9.2, R10.1, U3.3 (+), U3.5 (+), U4.3 (+), U4.5 (+)
V_SUPPLY: C3.1, C4.1, C5.1, R9.1, R13.2, U3.8 (V+), U4.8 (V+), U5.8 (V+), V_SUPPLY1.1, V_SUPPLY1.2, V_SUPPLY1.3, V_SUPPLY1.4, V_SUPPLY1.5

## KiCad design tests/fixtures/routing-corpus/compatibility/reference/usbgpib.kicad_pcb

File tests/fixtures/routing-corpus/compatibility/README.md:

# Retained source-compatibility boards

The previous routing Tiers 2–4 remain here with their original manifest entries,
project settings, normalized references, licenses and hash checks. They have
8 / 3 / 17 known structural blockers and are retained for importer/geometry
regression work. Their replacement routing inputs are documented in
`../alternatives/README.md`. No source rules or placements were edited.

Run the existing verifier with `--corpus tests/fixtures/routing-corpus/compatibility
--level all --preflight-only` and a fresh artifact destination. A successful
compatibility preflight checks the recorded allowances; it does not mean these
boards are physically valid or routed.

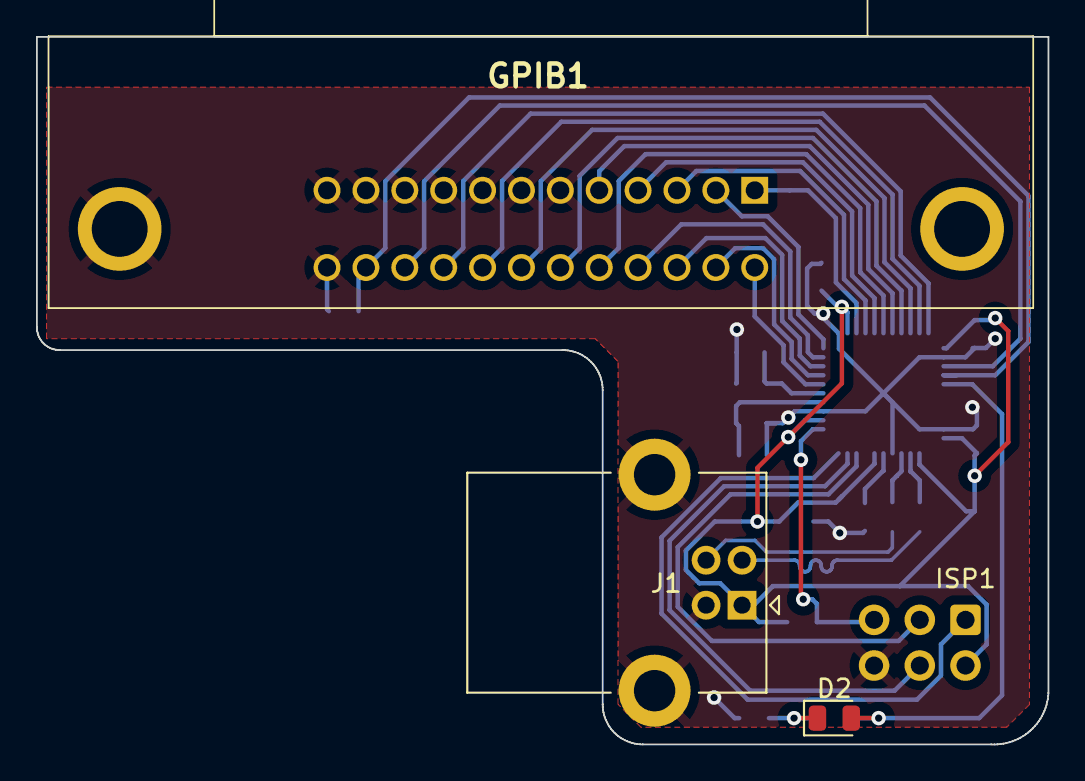
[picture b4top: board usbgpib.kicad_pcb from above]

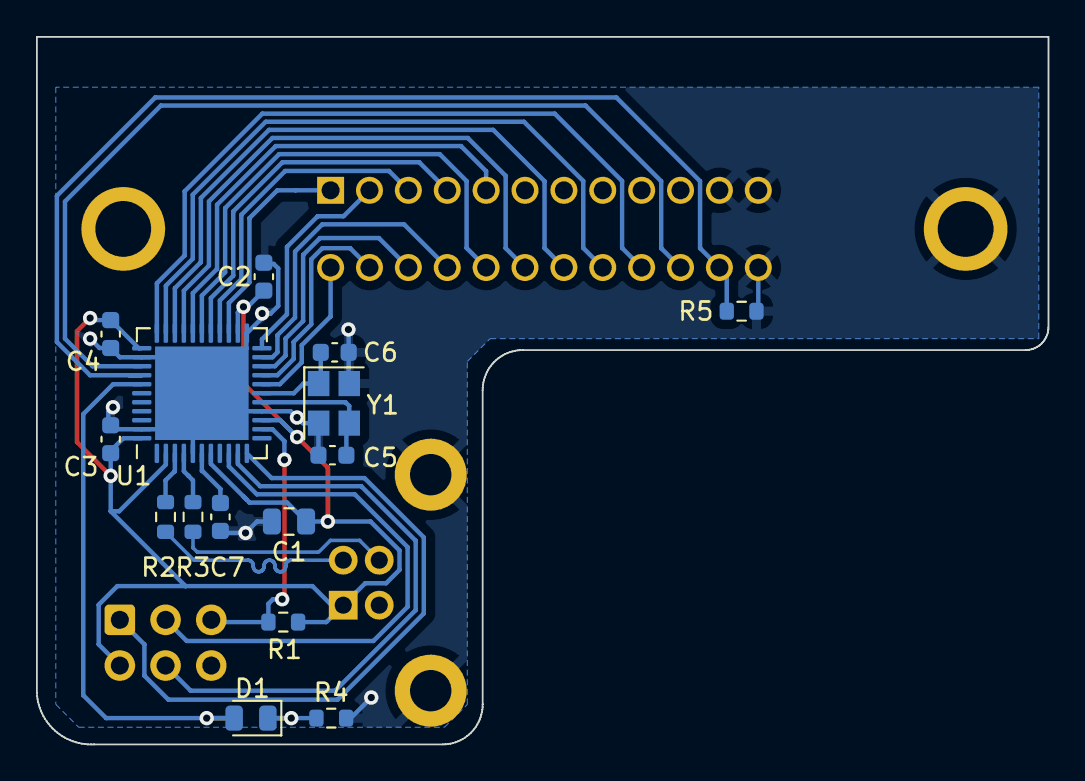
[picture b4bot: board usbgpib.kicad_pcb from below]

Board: 2 copper layers, 56.2 x 39.3 mm, 19 parts (15 on the bottom side), 31 nets.

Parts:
C1: 4.7uF; C_0805_2012Metric
C2, C3, C4: 100nF; C_0603_1608Metric
C5, C6: 22pf; C_0603_1608Metric
C7: 1u; C_0603_1608Metric
D1: LED; LED_0805_2012Metric
D2: DNP; LED_0805_2012Metric
GPIB1: 112-024-113R001; 112024113R001
ISP1: ISP; IDC-Header_2x03_P2.54mm_Vertical
J1: USB_B; USB_B_Lumberg_2411_02_Horizontal
R1: 10k; R_0603_1608Metric
R2, R3: 22R; R_0603_1608Metric
R4: 470R; R_0603_1608Metric
R5: 100k; R_0603_1608Metric
U1: ATmega32U4-MU; QFN-44-1EP_7x7mm_P0.5mm_EP5.2x5.2mm
Y1: Crystal_GND24; Crystal_SMD_3225-4Pin_3.2x2.5mm

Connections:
+5V: C1.1, C2.1, C3.1, C4.1, ISP1.2, J1.1, R1.1, U1.2, U1.7, U1.14, U1.24, U1.34, U1.44
/ATN: GPIB1.22, R5.1, U1.37
/DAV: GPIB1.12, U1.30
/DIO1: GPIB1.2, U1.18
/DIO2: GPIB1.4, U1.19
/DIO3: GPIB1.6, U1.20
/DIO4: GPIB1.8, U1.21
/DIO5: GPIB1.1, U1.25
/DIO6: GPIB1.3, U1.22
/DIO7: GPIB1.5, U1.26
/DIO8: GPIB1.7, U1.27
/EOI: GPIB1.10, U1.28
/IFC: GPIB1.18, U1.33
/MISO: ISP1.1, U1.11
/MOSI: ISP1.4, U1.10
/NDAC: GPIB1.16, U1.32
/NRFD: GPIB1.14, U1.31
/REN: GPIB1.9, U1.29
/SCK: ISP1.3, U1.9
/SRQ: GPIB1.20, U1.36
/USB_N: J1.2, R2.2
/USB_P: J1.3, R3.2
GND: C1.2, C2.2, C3.2, C4.2, C5.2, C6.2, C7.2, GPIB1.11, GPIB1.13, GPIB1.15, GPIB1.17, GPIB1.19, GPIB1.21, GPIB1.23, GPIB1.24, GPIB1.MH2, ISP1.6, J1.4, J1.5, R4.2, R5.2, U1.5, U1.15, U1.23, U1.35, U1.43, U1.45, Y1.2, Y1.4
unnamed: C5.1, U1.16, Y1.3
unnamed: C6.1, U1.17, Y1.1
unnamed: C7.1, U1.6
unnamed: D1.1, D2.1, R4.1
unnamed: D1.2, D2.2, U1.38
unnamed: ISP1.5, R1.2, U1.13
unnamed: R2.1, U1.3
unnamed: R3.1, U1.4

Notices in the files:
tests/fixtures/routing-corpus/reference/nascom_eprom_80bus.kicad_pcb:
Copyright (c) Codesqueak - 2025 - All Rights Reserved
